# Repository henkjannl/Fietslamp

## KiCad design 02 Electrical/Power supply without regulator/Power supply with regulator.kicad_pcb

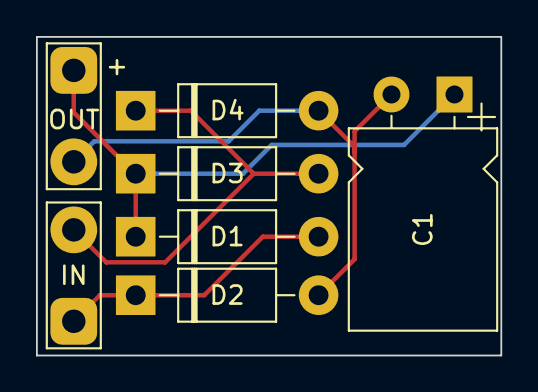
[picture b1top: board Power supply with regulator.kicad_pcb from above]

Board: 2 copper layers, 25.8 x 17.7 mm, 7 parts (0 on the bottom side), 4 nets.

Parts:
C1: 10uF; CP_Axial_L11.0mm_D8.0mm_P15.00mm_Horizontal
D1, D2, D3, D4: 1N4002; D_DO-41_SOD81_P10.16mm_Horizontal
IN: IN; TestPoint_2Pads_Pitch5.08mm_Drill1.3mm
OUT: 100; TestPoint_2Pads_Pitch5.08mm_Drill1.3mm

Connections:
0: C1.2, D2.2 (A), D4.2 (A), OUT.2
In: D1.2 (A), D2.1 (K), IN.1 (E1)
unnamed: D3.2 (A), D4.1 (K), IN.2 (E2)
Out: C1.1, D1.1 (K), D3.1 (K), OUT.1

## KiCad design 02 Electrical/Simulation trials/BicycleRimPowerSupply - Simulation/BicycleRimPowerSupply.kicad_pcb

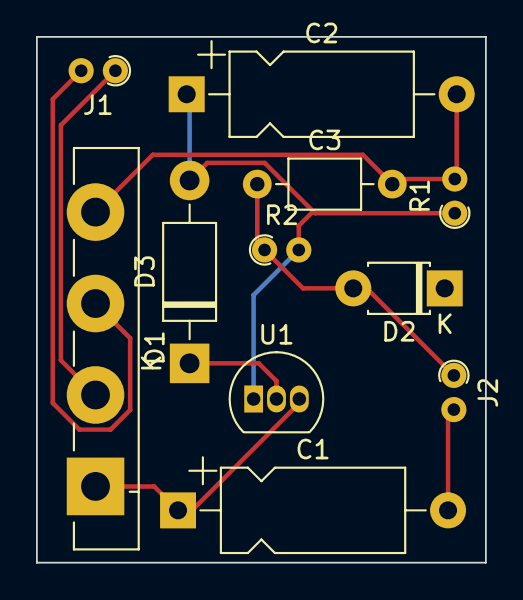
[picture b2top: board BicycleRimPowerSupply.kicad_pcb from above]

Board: 2 copper layers, 24.9 x 29.2 mm, 11 parts (0 on the bottom side), 6 nets.

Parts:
C1: 1000uF; CP_Axial_L10.0mm_D4.5mm_P15.00mm_Horizontal
C2: 10uF; CP_Axial_L10.0mm_D4.5mm_P15.00mm_Horizontal
C3: 1uF; C_Axial_L3.8mm_D2.6mm_P7.50mm_Horizontal
D1: GBU4B; Diode_Bridge_Vishay_GBU
D2: 1N4002; D_T-1_P5.08mm_Horizontal
D3: 1N4002; D_DO-41_SOD81_P10.16mm_Horizontal
J1, J2: Conn_01x02_Female; R_Axial_DIN0204_L3.6mm_D1.6mm_P1.90mm_Vertical
R1: 330; R_Axial_DIN0204_L3.6mm_D1.6mm_P1.90mm_Vertical
R2: 240; R_Axial_DIN0204_L3.6mm_D1.6mm_P1.90mm_Vertical
U1: LM317L_TO92; TO-92_Inline

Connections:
unnamed: C1.1, D1.1 (+), D2.1 (K), U1.3 (VI)
unnamed: C1.2, C2.2, C3.2, D1.4 (-), J2.2, R1.2
unnamed: C2.1, D3.2 (A), R1.1, R2.2, U1.1 (ADJ)
unnamed: C3.1, D2.2 (A), D3.1 (K), J2.1, R2.1, U1.2 (VO)
unnamed: D1.2, J1.1
unnamed: D1.3, J1.2

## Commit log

2022-02-19 Alternative light bulb found
2022-04-21 Power supply design added
2022-06-18 Simulations added
2022-07-16 Experiments with simulations
2022-07-18 First working simulation of regulated power supply
2022-07-20 PCB design
2022-08-17 Simulation added
